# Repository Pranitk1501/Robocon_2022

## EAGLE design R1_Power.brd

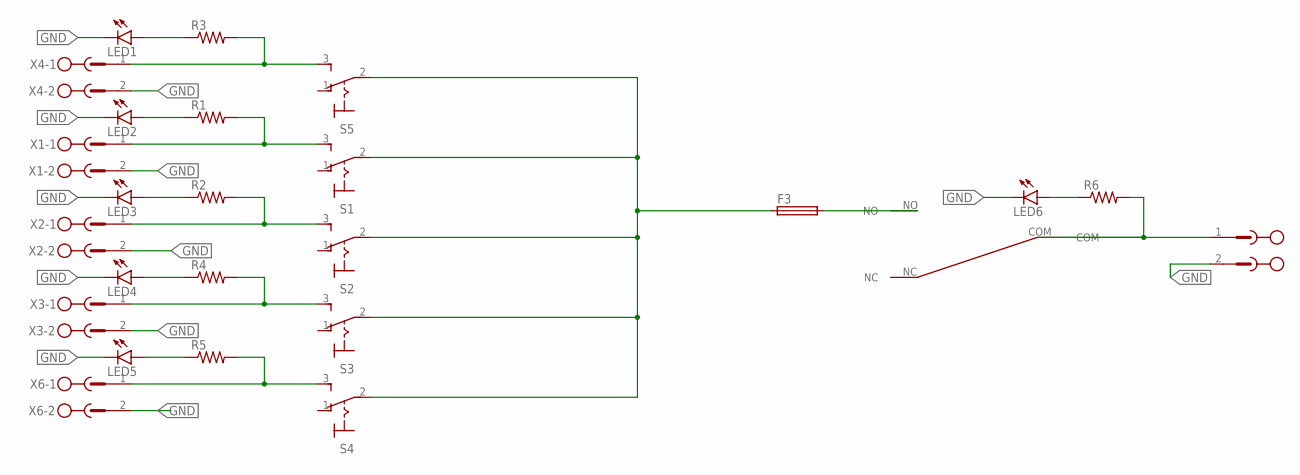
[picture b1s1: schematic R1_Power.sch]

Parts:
F3: SH22,5
LED1, LED2, LED3, LED4, LED5, LED6: LED3MM
MAINSWITCH: SPDT_TOGGLE_1SPDT_TOGGLE_2; SPDT_TOGGLE_1
R1, R2, R3, R4, R5, R6: R-US_0207/10; 0207/10
S1, S2, S3, S4, S5: 320-916
VCC: MSTBV2
X1, X2, X3, X4, X6: MSTBV2

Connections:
GND: LED1.K (C), LED2.K (C), LED3.K (C), LED4.K (C), LED5.K (C), LED6.K (C), VCC.2, X1.2, X2.2, X3.2, X4.2, X6.2
unnamed: F3.2, MAINSWITCH.NO
unnamed: F3.1, S1.2, S2.2, S3.2, S4.2, S5.2
unnamed: R3.2, S5.3 (S), X4.1
unnamed: LED1.A, R3.1
unnamed: R1.2, S1.3 (S), X1.1
unnamed: LED3.A, R2.1
unnamed: R2.2, S2.3 (S), X2.1
unnamed: LED6.A, R6.1
unnamed: MAINSWITCH.COM, R6.2, VCC.1
unnamed: LED4.A, R4.1
unnamed: R4.2, S3.3 (S), X3.1
unnamed: LED2.A, R1.1
unnamed: R5.2, S4.3 (S), X6.1
unnamed: LED5.A, R5.1

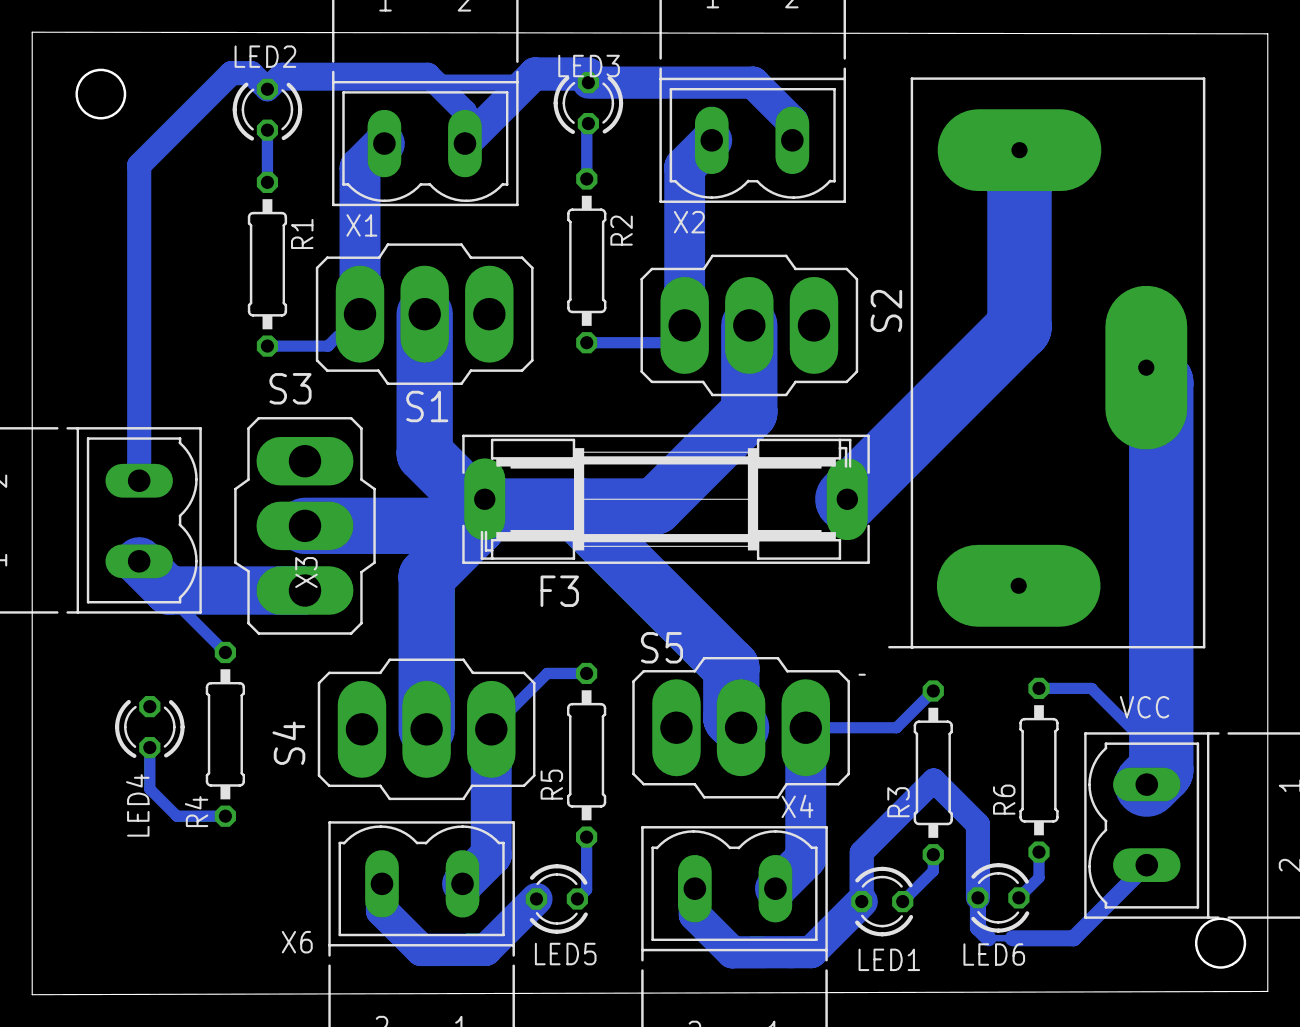
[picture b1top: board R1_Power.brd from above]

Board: 2 copper layers, 76.5 x 59.6 mm, 25 parts (0 on the bottom side), 15 nets.

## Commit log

2022-10-13 init commit
